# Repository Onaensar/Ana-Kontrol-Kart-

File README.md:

# Ana-Kontrol-Kart-
İDA Projesi için ana kontrol kartı devre ve pcb şeması

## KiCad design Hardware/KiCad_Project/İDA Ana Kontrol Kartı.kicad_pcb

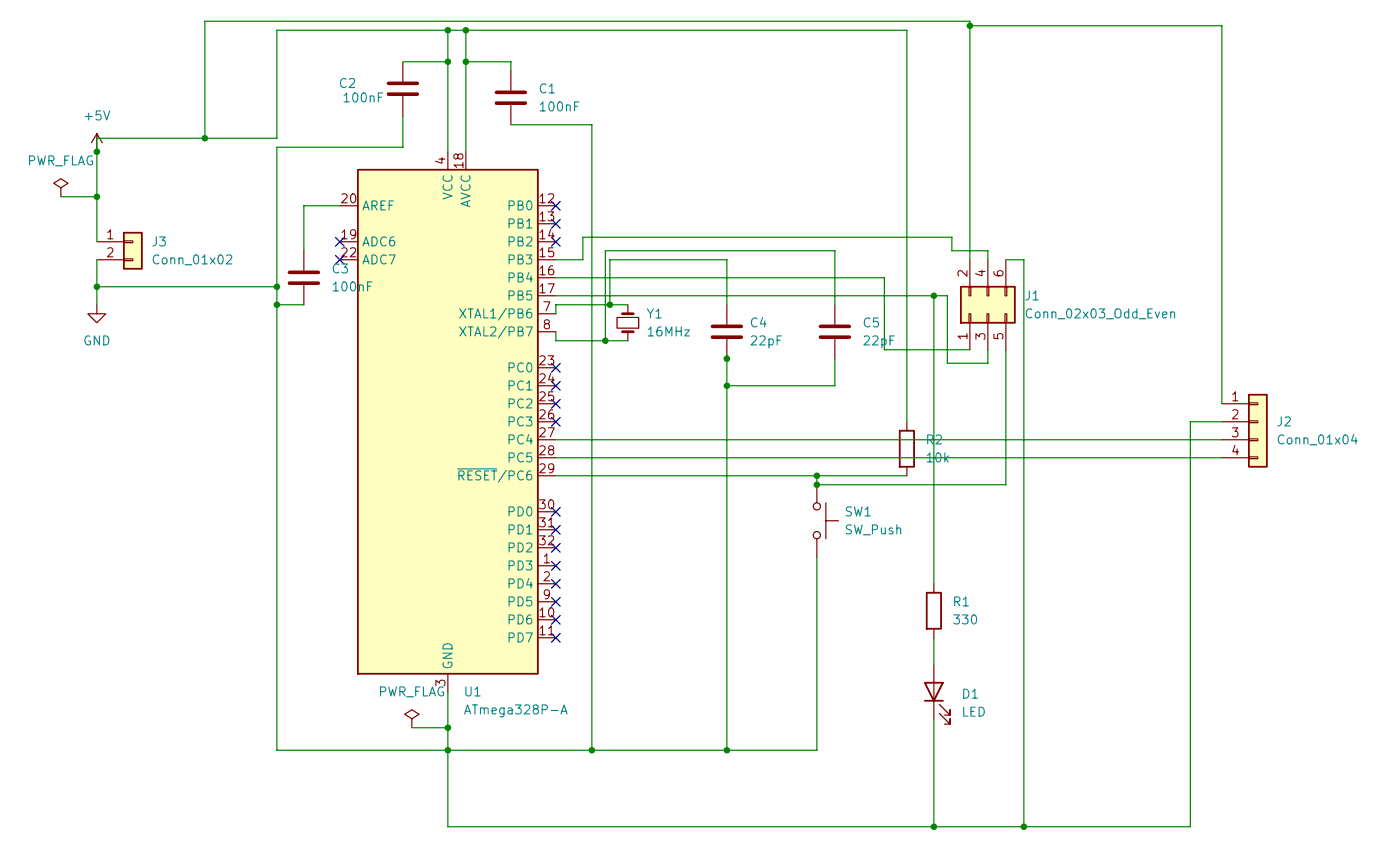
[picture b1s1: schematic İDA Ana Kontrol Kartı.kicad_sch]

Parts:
C1, C2, C3: 100nF; C_0805_2012Metric
C4, C5: 22pF; C_0805_2012Metric
D1: LED; LED_0805_2012Metric
J1: Conn_02x03_Odd_Even; PinHeader_2x03_P2.54mm_Vertical
J2: Conn_01x04; PinHeader_1x04_P2.54mm_Vertical
J3: Conn_01x02; PinHeader_1x02_P2.54mm_Vertical
R1: 330; R_0805_2012Metric
R2: 10k; R_0805_2012Metric
SW1: SW_Push; SW_PUSH_6mm
U1: ATmega328P-A; TQFP-32_7x7mm_P0.8mm
Y1: 16MHz; Crystal_SMD_5032-2Pin_5.0x3.2mm

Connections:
+5V: C1.1, C2.1, J1.2, J2.1, J3.1, R2.1, U1.4 (VCC), U1.6 (VCC), U1.18 (AVCC)
GND: C1.2, C2.2, C3.2, C4.2, C5.2, D1.1 (K), J1.6, J2.2, J3.2, SW1.2, U1.3 (GND), U1.5 (GND), U1.21 (GND)
unnamed: D1.2 (A), R1.2
unnamed: J1.1, U1.16 (PB4)
unnamed: J1.3, R1.1, U1.17 (PB5)
unnamed: J1.4, U1.15 (PB3)
unnamed: J1.5, R2.2, SW1.1, U1.29 (~RESET/PC6)
unnamed: J2.3, U1.27 (PC4)
unnamed: J2.4, U1.28 (PC5)
unnamed: C3.1, U1.20 (AREF)
unnamed: C4.1, U1.7 (XTAL1/PB6), Y1.2
unnamed: C5.1, U1.8 (XTAL2/PB7), Y1.1

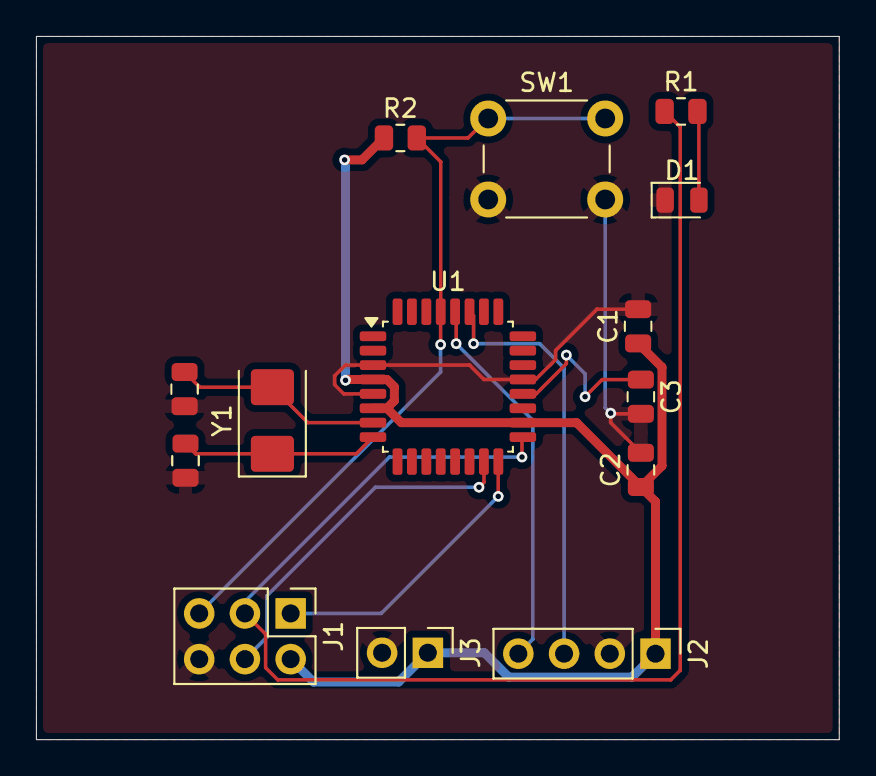
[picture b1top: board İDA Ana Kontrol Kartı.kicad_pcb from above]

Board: 2 copper layers, 44.6 x 39.1 mm, 14 parts (0 on the bottom side), 12 nets.

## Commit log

2026-06-15 Create KiCad_Project
